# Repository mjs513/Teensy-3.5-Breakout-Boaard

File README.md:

These are the final updates to the two breakout boards I tried for my first attempt at using kicad.  See https://forum.pjrc.com/threads/36244-Teensy-3-5-3-6-Breakout-board-to-test-things-with

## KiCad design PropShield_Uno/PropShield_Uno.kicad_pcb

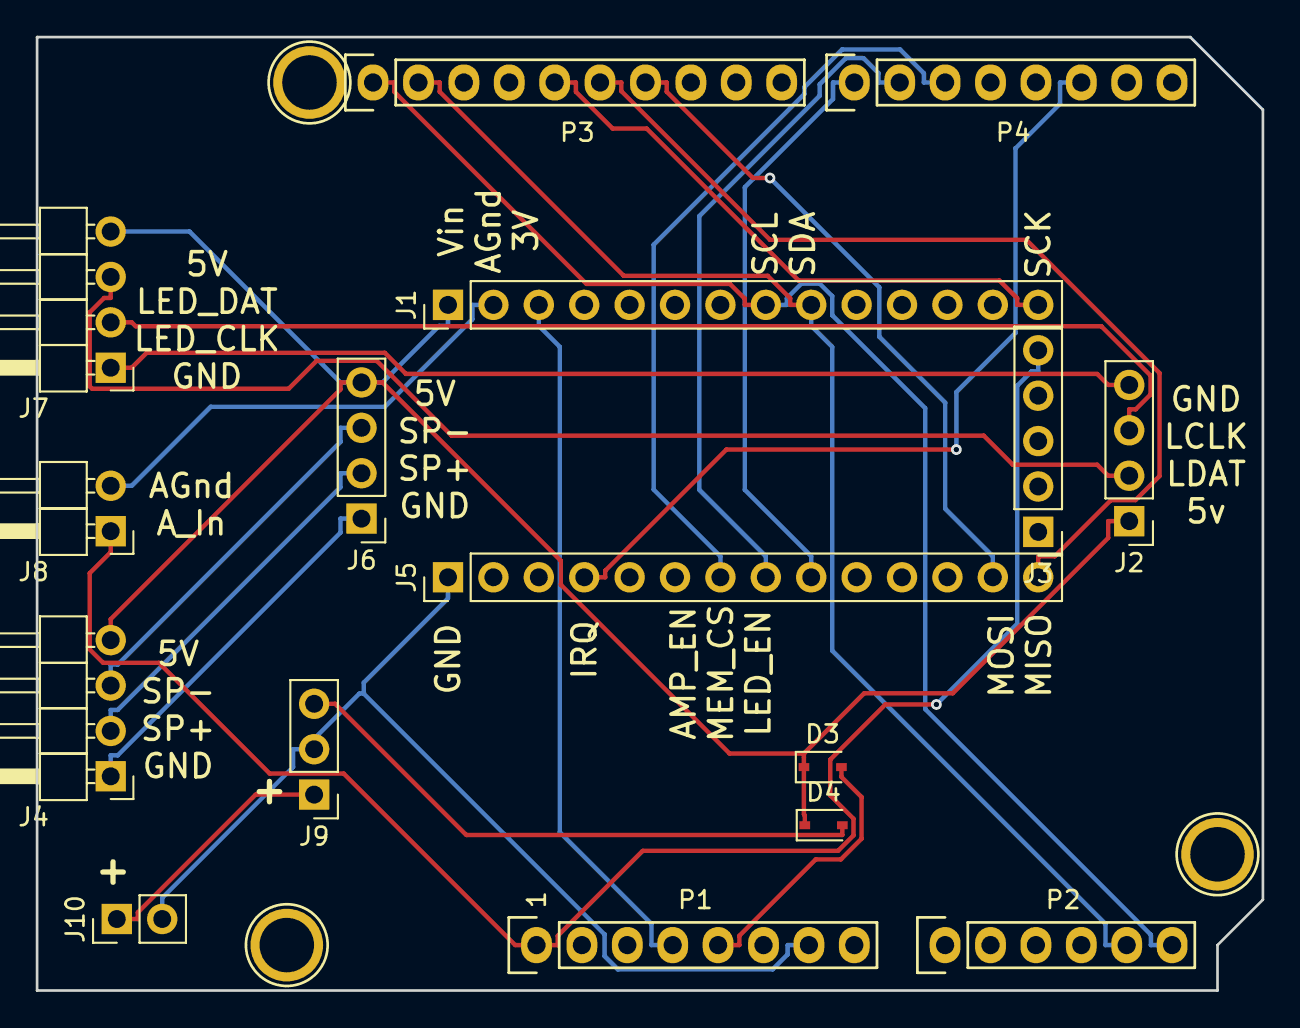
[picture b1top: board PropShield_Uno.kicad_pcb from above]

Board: 2 copper layers, 68.6 x 53.3 mm, 19 parts (0 on the bottom side), 23 nets.

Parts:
D3, D4: D_Schottky_ALT; D_SOD-323
J1, J5: CONN_01X14; Pin_Header_Straight_1x14_Pitch2.54mm
J2, J6: CONN_01X04; Pin_Header_Straight_1x04_Pitch2.54mm
J3: CONN_01X05; Pin_Header_Straight_1x05_Pitch2.54mm
J4, J7: CONN_01X04; Pin_Header_Angled_1x04_Pitch2.54mm
J8: CONN_01X02; Pin_Header_Angled_1x02_Pitch2.54mm
J9: CONN_01X03; Pin_Header_Straight_1x03_Pitch2.54mm
J10: CONN_01X02; Pin_Header_Straight_1x02_Pitch2.54mm
P1: Power; Socket_Strip_Arduino_1x08
P2: Analog; Socket_Strip_Arduino_1x06
P3: Digital; Socket_Strip_Arduino_1x10
P4: Digital; Socket_Strip_Arduino_1x08
P5, P6: CONN_01X01; Arduino_1pin
P7: CONN_02X03; Arduino_1pin

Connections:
+3V3: J1.3, P1.4
+5V: D3.2, P1.5
/2: J5.4, P4.6
/5(**): J5.7, P4.3
/6(**): J5.8, P4.2
/7: J5.9, P4.1
/11(**/MOSI): J5.13, P3.7
/12(MISO): J5.14, P3.6
/13(SCK): J1.14, P3.5
/A4(SDA): J1.9, P2.5, P3.2
/A5(SCL): J1.8, P2.6, P3.1
unnamed: D3.1, D4.1, J1.1, J2.1, J4.4, J6.4, J7.4
unnamed: D4.2, J9.3
unnamed: J1.2, J8.2
unnamed: J2.2, J7.3
unnamed: J2.3, J7.2
unnamed: J2.4, J7.1
unnamed: J3.5, J8.1, P1.1
unnamed: J4.1, J6.1
unnamed: J4.2, J6.2
unnamed: J4.3, J6.3
unnamed: J9.1, J10.1
unnamed: J5.1, J9.2, J10.2, P1.7

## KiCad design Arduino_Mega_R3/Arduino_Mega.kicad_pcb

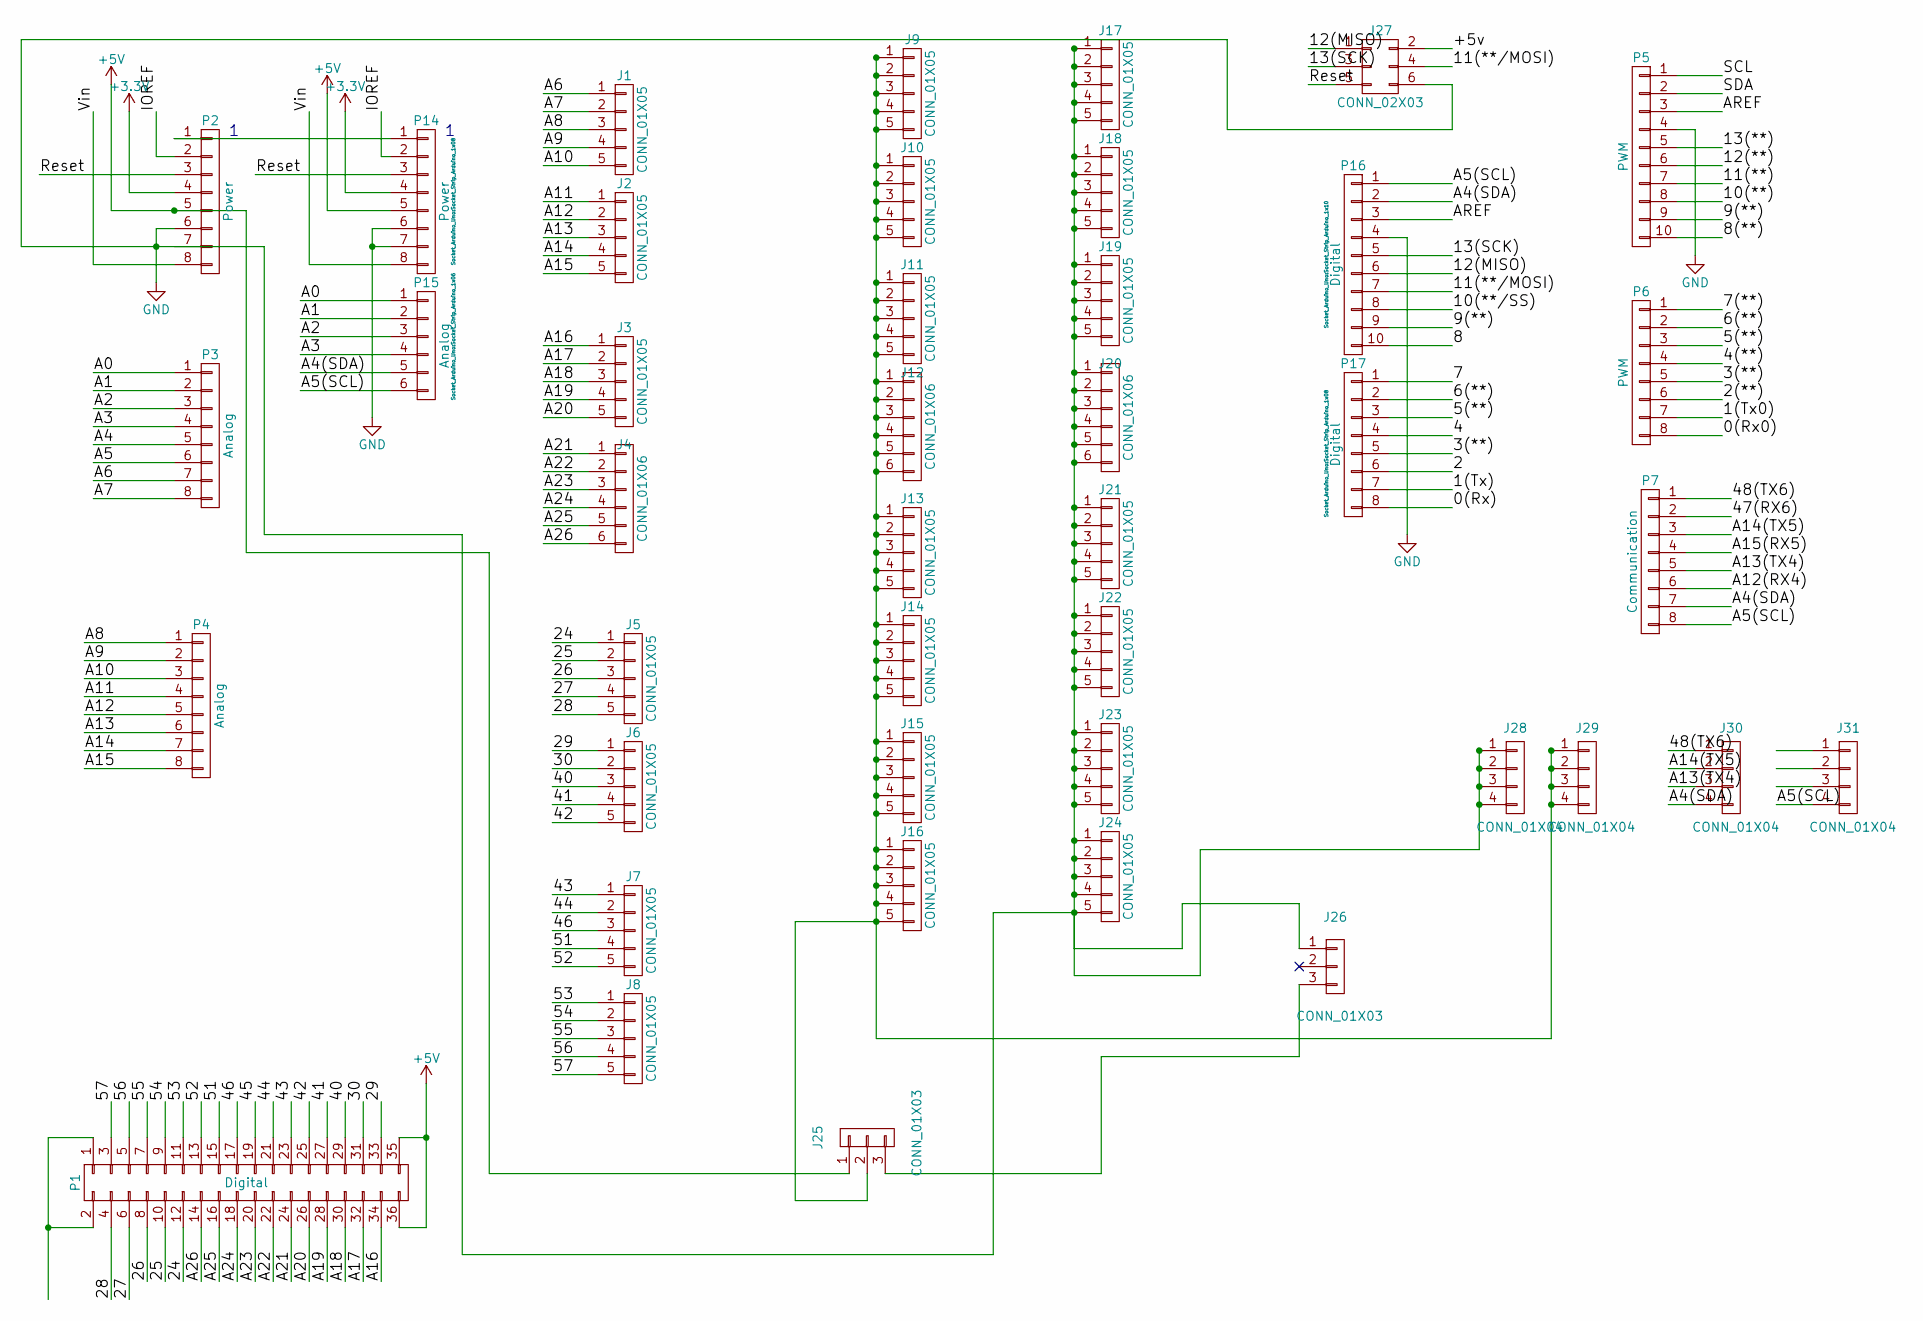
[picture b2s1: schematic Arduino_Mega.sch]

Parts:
J1, J2, J3, J5, J6, J7, J8, J9, J10, J11, J13, J14, J15, J16, J17, J18, J19, J21, J22, J23, J24: CONN_01X05; Pin_Header_Straight_1x05_Pitch2.54mm
J4, J12, J20: CONN_01X06; Pin_Header_Straight_1x06_Pitch2.54mm
J25, J26: CONN_01X03; Pin_Header_Straight_1x03_Pitch2.54mm
J27: CONN_02X03; Pin_Header_Straight_2x03_Pitch2.54mm
J28, J29, J30, J31: CONN_01X04; Pin_Header_Straight_1x04_Pitch2.54mm
P1: Digital; Socket_Strip_Arduino_2x18
P2, P14: Power; Socket_Strip_Arduino_1x08
P3, P4: Analog; Socket_Strip_Arduino_1x08
P5: PWM; Socket_Strip_Arduino_1x10
P6: PWM; Socket_Strip_Arduino_1x08
P7: Communication; Socket_Strip_Arduino_1x08
P15: Analog; Socket_Strip_Arduino_1x06
P16: Digital; Socket_Strip_Arduino_1x10
P17: Digital; Socket_Strip_Arduino_1x08

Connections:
+3V3: P2.4, P14.4
+5V: J25.1, J27.2, P1.35, P1.36, P2.5, P14.5
/0(Rx0): P6.8
/0(Rx): P17.8
/1(Tx0): P6.7
/1(Tx): P17.7
/2: P17.6
/2(**): P6.6
/3(**): P6.5, P17.5
/4: P17.4
/4(**): P6.4
/5(**): P6.3, P17.3
/6(**): P6.2, P17.2
/7: P17.1
/7(**): P6.1
/8: P16.10
/8(**): P5.10
/9(**): P5.9, P16.9
/10(**): P5.8
/10(**/SS): P16.8
/11(**): P5.7
/11(**/MOSI): J27.4, P16.7
/12(**): P5.6
/12(MISO): J27.1, P16.6
/13(**): P5.5
/13(SCK): J27.3, P16.5
/24: J5.1, P1.12
/25: J5.2, P1.10
/26: J5.3, P1.8
/27: J5.4, P1.6
/28: J5.5, P1.4
/29: J6.1, P1.33
/30: J6.2, P1.31
/40: J6.3, P1.29
/41: J6.4, P1.27
/42: J6.5, P1.25
/43: J7.1, P1.23
/44: J7.2, P1.21
/45: P1.19
/46: J7.3, P1.17
/47(RX6): P7.2
/48(TX6): J30.1, P7.1
/51: J7.4, P1.15
/52: J7.5, P1.13
/53: J8.1, P1.11
/54: J8.2, P1.9
/55: J8.3, P1.7
/56: J8.4, P1.5
/57: J8.5, P1.3
/A0: P3.1, P15.1
/A1: P3.2, P15.2
/A2: P3.3, P15.3
/A3: P3.4, P15.4
/A4: P3.5
/A4(SDA): J30.4, P7.7, P15.5, P16.2
/A5: P3.6
/A5(SCL): J31.4, P7.8, P15.6, P16.1
/A6: J1.1, P3.7
/A7: J1.2, P3.8
/A8: J1.3, P4.1
/A9: J1.4, P4.2
/A10: J1.5, P4.3
/A11: J2.1, P4.4
/A12: J2.2, P4.5
/A12(RX4): P7.6
/A13: J2.3, P4.6
/A13(TX4): J30.3, P7.5
/A14: J2.4, P4.7
/A14(TX5): J30.2, P7.3
/A15: J2.5, P4.8
/A15(RX5): P7.4
/A16: J3.1, P1.34
/A17: J3.2, P1.32
/A18: J3.3, P1.30
/A19: J3.4, P1.28
/A20: J3.5, P1.26
/A21: J4.1, P1.24
/A22: J4.2, P1.22
/A23: J4.3, P1.20
/A24: J4.4, P1.18
/A25: J4.5, P1.16
/A26: J4.6, P1.14
/AREF: P5.3, P16.3
/IOREF: P2.2, P14.2
/Reset: J27.5, P2.3, P14.3
/SCL: P5.1
/SDA: P5.2
/Vin: P2.8, P14.8
GND: J17.1, J17.2, J17.3, J17.4, J17.5, J18.1, J18.2, J18.3, J18.4, J18.5, J19.1, J19.2, J19.3, J19.4, J19.5, J20.1, J20.2, J20.3, J20.4, J20.5, J20.6, J21.1, J21.2, J21.3, J21.4, J21.5, J22.1, J22.2, J22.3, J22.4, J22.5, J23.1, J23.2, J23.3, J23.4, J23.5, J24.1, J24.2, J24.3, J24.4, J24.5, J26.1, J27.6, J28.1, J28.2, J28.3, J28.4, P2.6, P5.4, P14.6, P14.7, P16.4
unnamed: J9.1, J9.2, J9.3, J9.4, J9.5, J10.1, J10.2, J10.3, J10.4, J10.5, J11.1, J11.2, J11.3, J11.4, J11.5, J12.1, J12.2, J12.3, J12.4, J12.5, J12.6, J13.1, J13.2, J13.3, J13.4, J13.5, J14.1, J14.2, J14.3, J14.4, J14.5, J15.1, J15.2, J15.3, J15.4, J15.5, J16.1, J16.2, J16.3, J16.4, J16.5, J25.2, J29.1, J29.2, J29.3, J29.4
unnamed: J25.3, J26.3
unnamed: P1.1, P1.2
unnamed: P2.1, P14.1

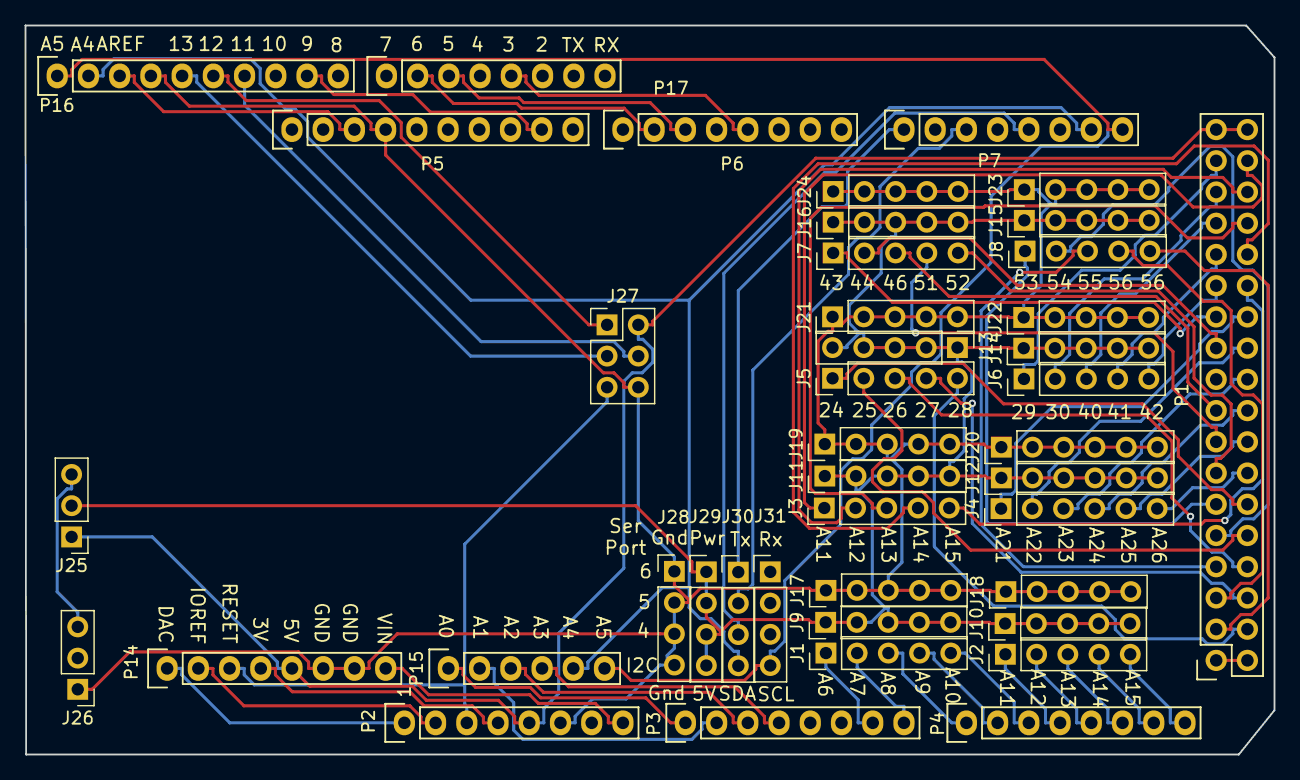
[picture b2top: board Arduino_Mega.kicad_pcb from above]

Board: 2 copper layers, 101.6 x 59.3 mm, 42 parts (0 on the bottom side), 68 nets.

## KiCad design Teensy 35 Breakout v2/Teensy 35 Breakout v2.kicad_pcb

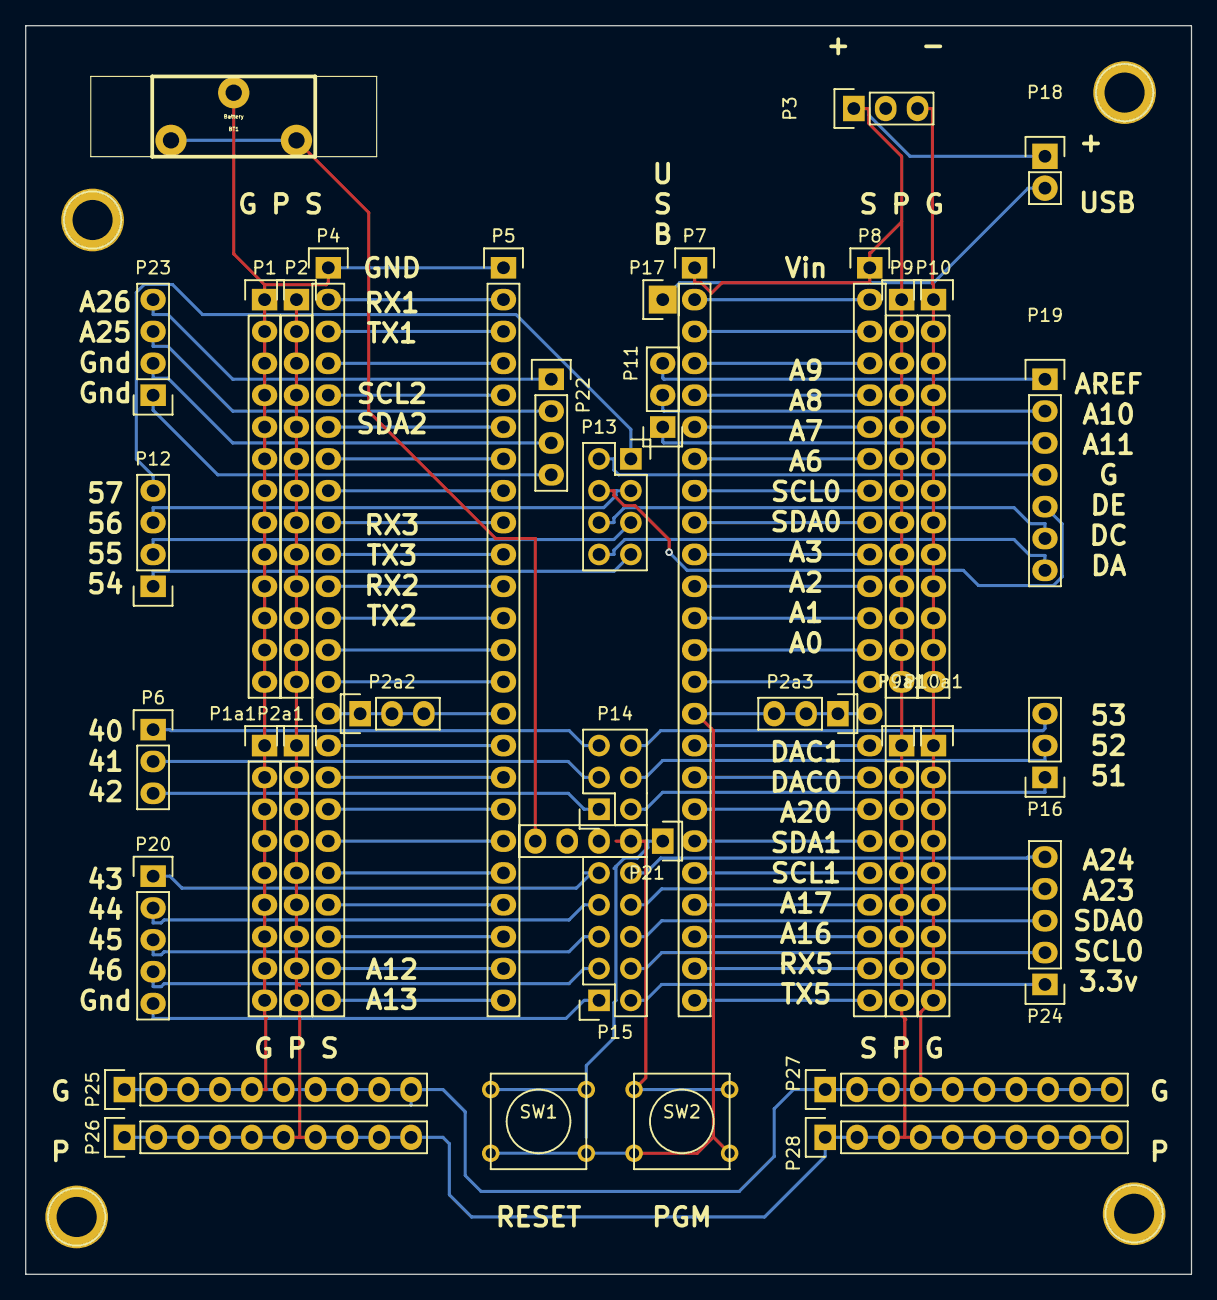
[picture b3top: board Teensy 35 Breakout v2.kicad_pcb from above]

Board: 2 copper layers, 93.0 x 99.6 mm, 41 parts (0 on the bottom side), 83 nets.

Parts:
BT1: Battery; BAT_HOLDER_2032
P1, P2, P9, P10: CONN_01X13; Pin_Header_Straight_1x13
P1a1, P2a1, P9a1: CONN_01X09; Pin_Header_Straight_1x09
P2a2, P2a3, P3, P6, P16: CONN_01X03; Pin_Header_Straight_1x03
P4, P8: CONN_01X24; Pin_Header_Straight_1x24
P5, P7: CONN_01X24; Socket_Strip_Straight_1x24
P10a1: CONN_01X10; Pin_Header_Straight_1x09
P11: CONN_01X03; Socket_Strip_Straight_1x03
P12, P23: CONN_01X04; Pin_Header_Straight_1x04
P13: CONN_02X04; Socket_Strip_Straight_2x04
P14: CONN_02X03; Socket_Strip_Straight_2x03
P15: CONN_02X05; Socket_Strip_Straight_2x05
P17: CONN_01X01; Socket_Strip_Straight_1x01
P18: CONN_01X02; Pin_Header_Straight_1x02
P19: CONN_01X08; Pin_Header_Straight_1x07
P20, P24: CONN_01X05; Pin_Header_Straight_1x05
P21: CONN_01X05; Socket_Strip_Straight_1x05
P22: CONN_01X04; Socket_Strip_Straight_1x04
P25, P26, P27, P28: CONN_01X10; Pin_Header_Straight_1x10
RE4: 1pin
REF1, REF2, REF3: 1pin
SW1, SW2: SW_PUSH_SMALL_H; SW_PUSH_SMALL

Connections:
unnamed: BT1.1, P21.5
unnamed: BT1.2, P1.1, P1.2, P1.3, P1.4, P1.5, P1.6, P1.7, P1.8, P1.9, P1.10, P1.11, P1.12, P1.13, P1a1.1, P1a1.2, P1a1.3, P1a1.4, P1a1.5, P1a1.6, P1a1.7, P1a1.8, P1a1.9, P3.3, P4.1, P5.1, P10.1, P10.2, P10.3, P10.4, P10.5, P10.6, P10.7, P10.8, P10.9, P10.10, P10.11, P10.12, P10.13, P10a1.1, P10a1.2, P10a1.3, P10a1.4, P10a1.5, P10a1.6, P10a1.7, P10a1.8, P10a1.9, P25.1, P25.2, P25.3, P25.4, P25.5, P25.6, P25.7, P25.8, P25.9, P25.10, P27.1, P27.2, P27.3, P27.4, P27.5, P27.6, P27.7, P27.8, P27.9, P27.10
unnamed: P2a2.1, P2a2.2, P2a2.3, P4.15, P5.15
unnamed: P2a3.1, P2a3.2, P2a3.3, P7.15, P8.15, SW1.2, SW2.2
unnamed: P4.2, P5.2
unnamed: P4.3, P5.3
unnamed: P4.4, P5.4
unnamed: P4.5, P5.5
unnamed: P4.6, P5.6
unnamed: P4.7, P5.7
unnamed: P4.8, P5.8
unnamed: P4.9, P5.9
unnamed: P4.10, P5.10
unnamed: P4.11, P5.11
unnamed: P4.12, P5.12
unnamed: P4.13, P5.13
unnamed: P4.14, P5.14
unnamed: P4.16, P5.16
unnamed: P4.17, P5.17
unnamed: P4.18, P5.18
unnamed: P4.19, P5.19
unnamed: P4.20, P5.20
unnamed: P4.21, P5.21
unnamed: P4.22, P5.22
unnamed: P4.23, P5.23
unnamed: P4.24, P5.24
unnamed: P7.2, P8.2
unnamed: P7.3, P8.3
unnamed: P7.4, P8.4
unnamed: P7.5, P8.5
unnamed: P7.6, P8.6
unnamed: P7.7, P8.7
unnamed: P7.8, P8.8
unnamed: P7.9, P8.9
unnamed: P7.10, P8.10
unnamed: P7.11, P8.11
unnamed: P7.12, P8.12
unnamed: P7.13, P8.13
unnamed: P7.14, P8.14
unnamed: P7.16, P8.16
unnamed: P7.17, P8.17
unnamed: P7.18, P8.18
unnamed: P7.19, P8.19
unnamed: P7.20, P8.20
unnamed: P7.21, P8.21
unnamed: P7.22, P8.22
unnamed: P7.23, P8.23
unnamed: P7.24, P8.24
unnamed: P11.1, P19.3
unnamed: P11.2, P19.2
unnamed: P11.3, P19.1
unnamed: P12.1, P13.7
unnamed: P12.2, P13.5
unnamed: P12.3, P13.3
unnamed: P12.4, P13.1
unnamed: P13.2, P19.4
unnamed: P13.4, P19.5
unnamed: P13.6, P19.6
unnamed: P13.8, P19.7
unnamed: P6.3, P14.1
unnamed: P14.2, P16.1
unnamed: P6.2, P14.3
unnamed: P14.4, P16.2
unnamed: P6.1, P14.5
unnamed: P14.6, P16.3
unnamed: P15.1, P20.5
unnamed: P15.2, P24.1
unnamed: P15.3, P20.4
unnamed: P15.4, P24.2
unnamed: P15.5, P20.3
unnamed: P15.6, P24.3
unnamed: P15.7, P20.2
unnamed: P15.8, P24.4
unnamed: P15.9, P20.1
unnamed: P15.10, P24.5
unnamed: P17.1, P18.2
unnamed: P2.1, P2.2, P2.3, P2.4, P2.5, P2.6, P2.7, P2.8, P2.9, P2.10, P2.11, P2.12, P2.13, P2a1.1, P2a1.2, P2a1.3, P2a1.4, P2a1.5, P2a1.6, P2a1.7, P2a1.8, P2a1.9, P3.1, P8.1, P9.1, P9.2, P9.3, P9.4, P9.5, P9.6, P9.7, P9.8, P9.9, P9.10, P9.11, P9.12, P9.13, P9a1.1, P9a1.2, P9a1.3, P9a1.4, P9a1.5, P9a1.6, P9a1.7, P9a1.8, P9a1.9, P18.1, P26.1, P26.2, P26.3, P26.4, P26.5, P26.6, P26.7, P26.8, P26.9, P26.10, P28.1, P28.2, P28.3, P28.4, P28.5, P28.6, P28.7, P28.8, P28.9, P28.10
unnamed: P21.1, SW1.1
unnamed: P21.2, SW2.1
unnamed: P22.1, P23.4
unnamed: P22.2, P23.3
unnamed: P22.3, P23.2
unnamed: P22.4, P23.1

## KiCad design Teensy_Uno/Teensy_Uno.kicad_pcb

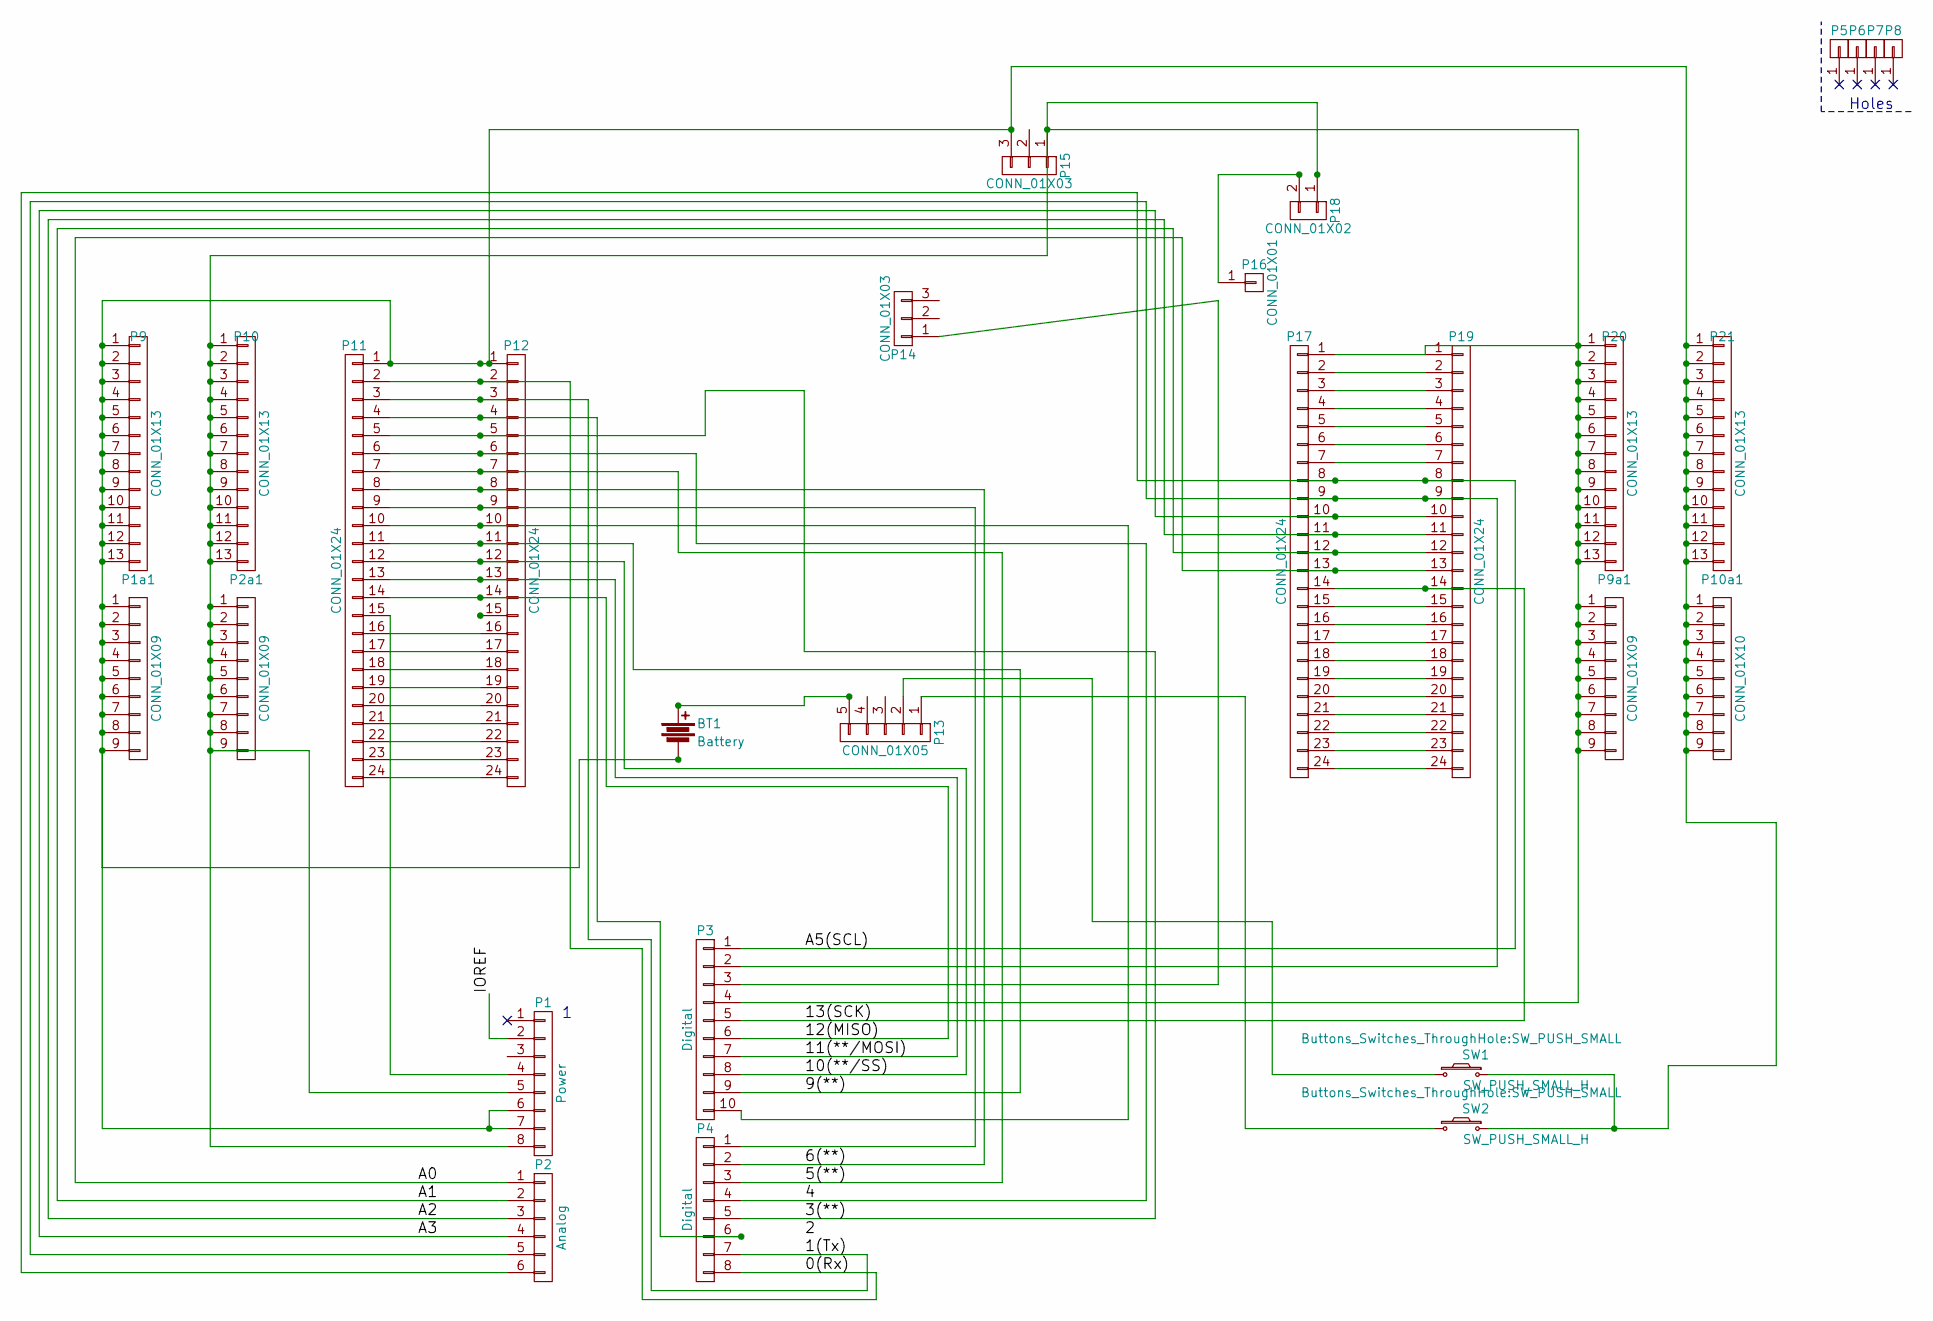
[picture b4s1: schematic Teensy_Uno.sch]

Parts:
BT1: Battery; BAT_HOLDER_2032
P1: Power; Socket_Strip_Arduino_1x08
P1a1, P2a1, P9a1: CONN_01X09; Pin_Header_Straight_1x09
P2: Analog; Socket_Strip_Arduino_1x06
P3: Digital; Socket_Strip_Arduino_1x10
P4: Digital; Socket_Strip_Arduino_1x08
P5, P6, P7, P8: CONN_01X01; Arduino_1pin
P9, P10, P20, P21: CONN_01X13; Pin_Header_Straight_1x13
P10a1: CONN_01X10; Pin_Header_Straight_1x09
P11, P19: CONN_01X24; Pin_Header_Straight_1x24
P12, P17: CONN_01X24; Socket_Strip_Straight_1x24
P13: CONN_01X05; Socket_Strip_Straight_1x05
P14: CONN_01X03; Socket_Strip_Straight_1x03
P15: CONN_01X03; Pin_Header_Straight_1x03
P16: CONN_01X01; Socket_Strip_Straight_1x01
P18: CONN_01X02; Pin_Header_Straight_1x02
SW1, SW2: SW_PUSH_SMALL_H; SW_PUSH_SMALL

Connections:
/0(Rx): P4.8, P11.2, P12.2
/1(Tx): P4.7, P11.3, P12.3
/3(**): P4.5, P11.5, P12.5
/4: P4.4, P11.6, P12.6
/5(**): P4.3, P11.7, P12.7
/6(**): P4.2, P11.8, P12.8
/9(**): P3.9, P11.11, P12.11
/10(**/SS): P3.8, P11.12, P12.12
/11(**/MOSI): P3.7, P11.13, P12.13
/12(MISO): P3.6, P11.14, P12.14
/13(SCK): P3.5, P17.14, P19.14
/A0: P2.1, P17.13, P19.13
/A1: P2.2, P17.12, P19.12
/A2: P2.3, P17.11, P19.11
/A3: P2.4, P17.10, P19.10
/A5(SCL): P2.6, P3.1, P17.8, P19.8
/IOREF: P1.2
unnamed: BT1.1, P13.5
unnamed: BT1.2, P1.6, P1.7, P1a1.1, P1a1.2, P1a1.3, P1a1.4, P1a1.5, P1a1.6, P1a1.7, P1a1.8, P1a1.9, P9.1, P9.2, P9.3, P9.4, P9.5, P9.6, P9.7, P9.8, P9.9, P9.10, P9.11, P9.12, P9.13, P10a1.1, P10a1.2, P10a1.3, P10a1.4, P10a1.5, P10a1.6, P10a1.7, P10a1.8, P10a1.9, P11.1, P12.1, P15.3, P21.1, P21.2, P21.3, P21.4, P21.5, P21.6, P21.7, P21.8, P21.9, P21.10, P21.11, P21.12, P21.13, SW1.2, SW2.2
unnamed: P1.4, P11.15
unnamed: P1.5, P1.8, P2a1.1, P2a1.2, P2a1.3, P2a1.4, P2a1.5, P2a1.6, P2a1.7, P2a1.8, P2a1.9, P3.4, P9a1.1, P9a1.2, P9a1.3, P9a1.4, P9a1.5, P9a1.6, P9a1.7, P9a1.8, P9a1.9, P10.1, P10.2, P10.3, P10.4, P10.5, P10.6, P10.7, P10.8, P10.9, P10.10, P10.11, P10.12, P10.13, P15.1, P17.1, P18.1, P19.1, P20.1, P20.2, P20.3, P20.4, P20.5, P20.6, P20.7, P20.8, P20.9, P20.10, P20.11, P20.12, P20.13
unnamed: P4.6, P11.4, P12.4
unnamed: P4.1, P11.9, P12.9
unnamed: P3.10, P11.10, P12.10
unnamed: P11.16, P12.16
unnamed: P11.17, P12.17
unnamed: P11.18, P12.18
unnamed: P11.19, P12.19
unnamed: P11.20, P12.20
unnamed: P11.21, P12.21
unnamed: P11.22, P12.22
unnamed: P11.23, P12.23
unnamed: P11.24, P12.24
unnamed: P13.1, SW2.1
unnamed: P13.2, SW1.1
unnamed: P3.3, P14.1
unnamed: P16.1, P18.2
unnamed: P17.2, P19.2
unnamed: P17.3, P19.3
unnamed: P17.4, P19.4
unnamed: P17.5, P19.5
unnamed: P17.6, P19.6
unnamed: P17.7, P19.7
unnamed: P2.5, P3.2, P17.9, P19.9
unnamed: P17.15, P19.15
unnamed: P17.16, P19.16
unnamed: P17.17, P19.17
unnamed: P17.18, P19.18
unnamed: P17.19, P19.19
unnamed: P17.20, P19.20
unnamed: P17.21, P19.21
unnamed: P17.22, P19.22
unnamed: P17.23, P19.23
unnamed: P17.24, P19.24

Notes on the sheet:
Holes

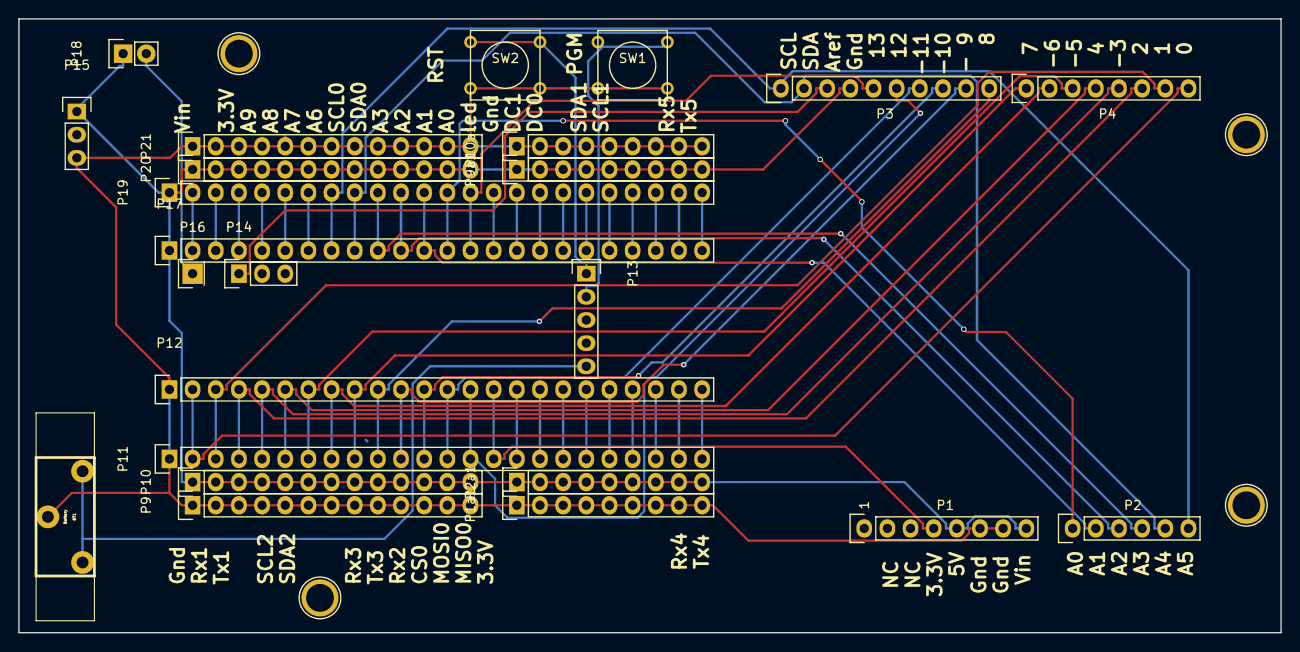
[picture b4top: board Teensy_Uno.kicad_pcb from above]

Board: 2 copper layers, 138.4 x 67.3 mm, 28 parts (0 on the bottom side), 53 nets.

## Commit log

2016-10-09 Initial Upload of v2
    This is the initial board design for a Teensy 3.5 breakout board.
2016-10-26 Version 2
2016-10-26 Updated readmw
2016-11-12 Cleanup V1 and added Uno footprint version
2016-11-18 fixed connection issues
2016-11-21 corrected reset voltage to 3.3v
2016-12-01 Additional corrections
2016-12-08 Final updates and corrections
2016-12-11 Correcyrf some connections
2017-06-15 Reinitialize repository
2017-07-22 Design Update
